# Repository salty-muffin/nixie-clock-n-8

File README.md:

# nixie-clock-n-8
a nixie clock built around 4 IN-8 tubes and an INS-3 dot

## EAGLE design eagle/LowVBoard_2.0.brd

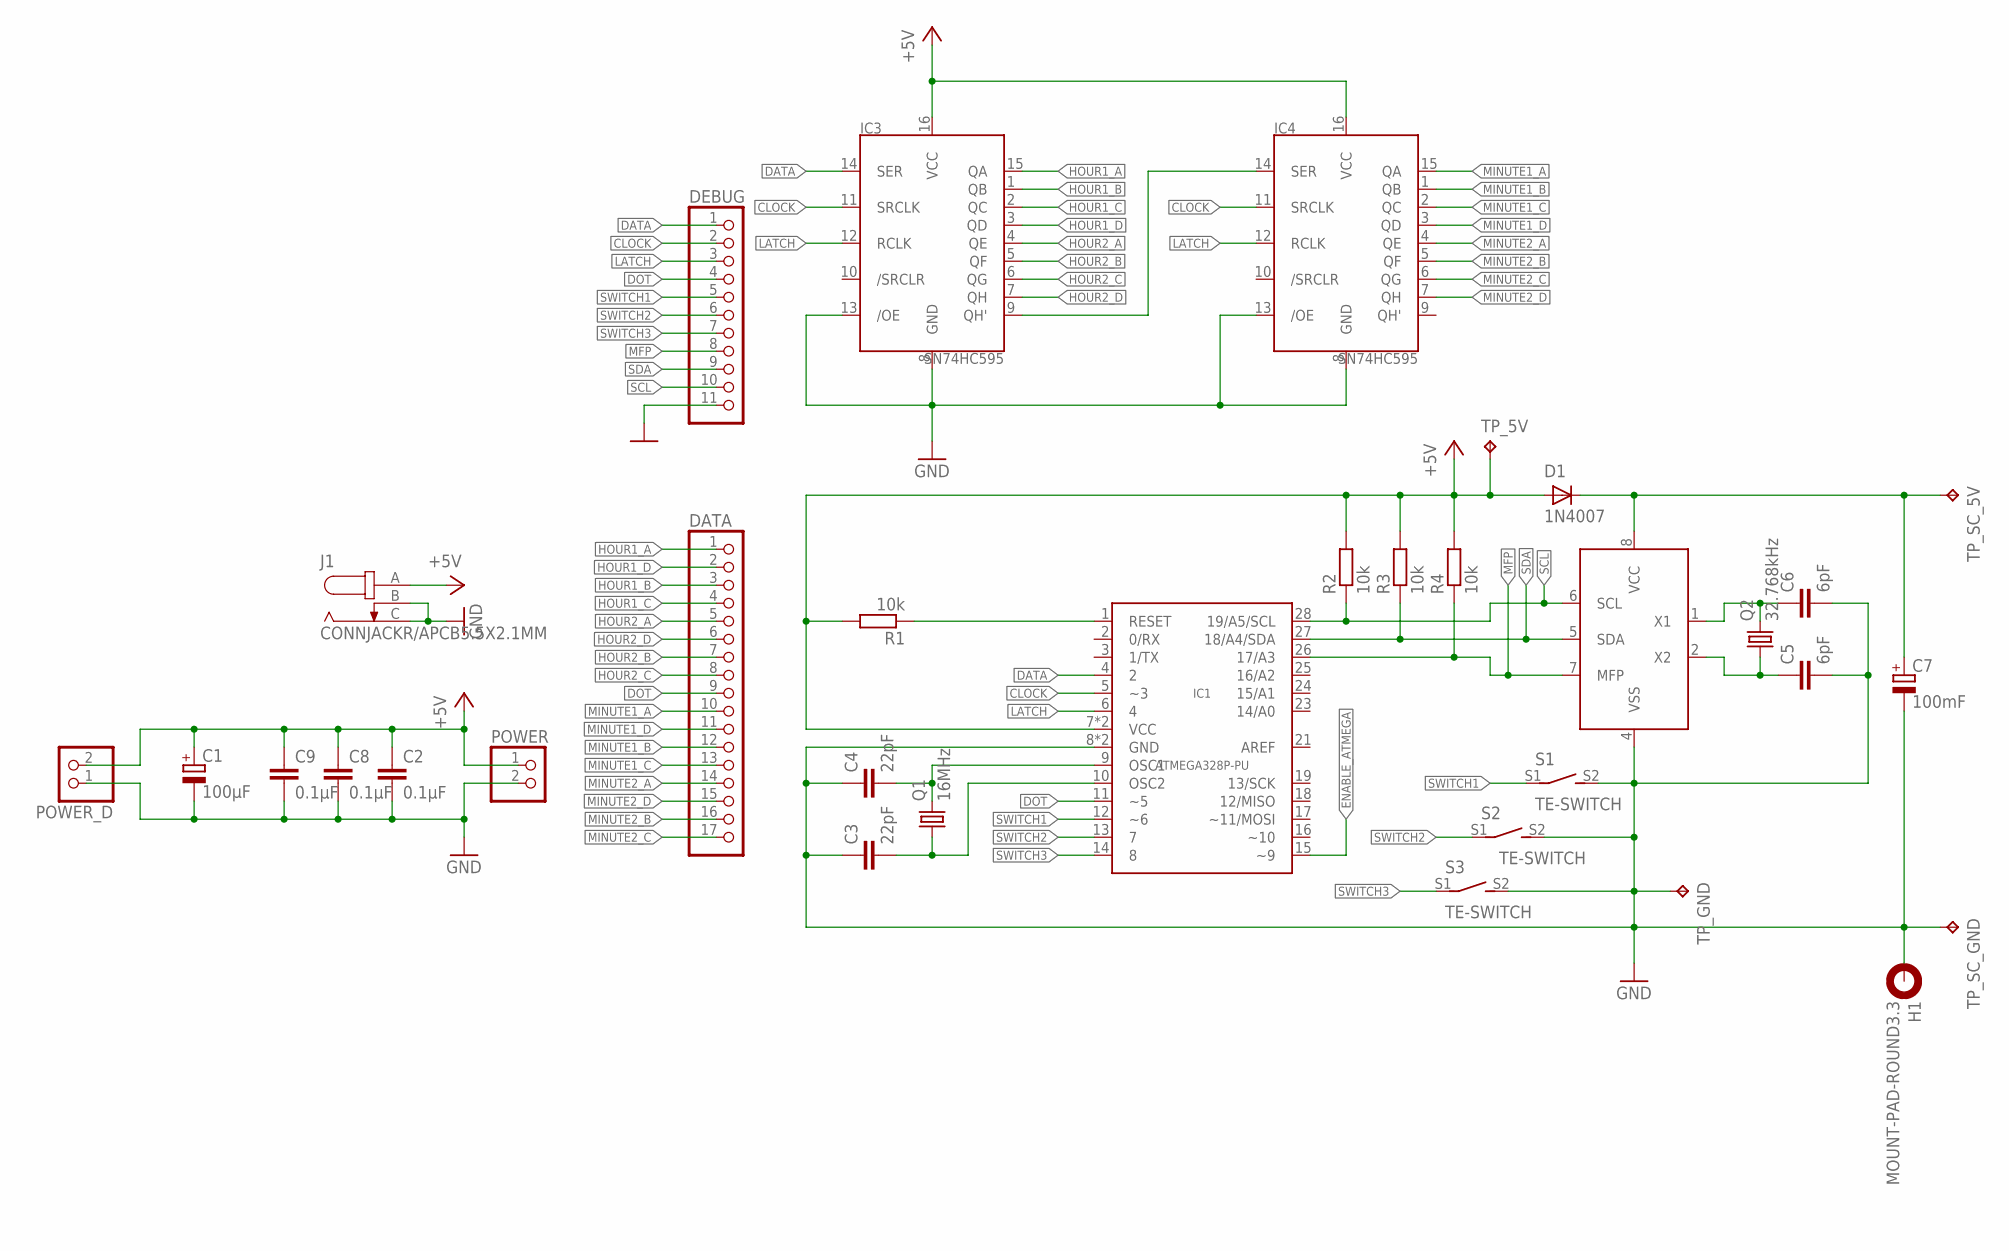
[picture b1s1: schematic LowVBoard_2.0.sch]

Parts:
C1: 100µF; E2-5
C2, C8, C9: 0.1µF; C025-024X044
C3, C4: 22pF; C025-024X044
C5, C6: 6pF; C025-024X044
C7: 100mF; SUPERCAP-11.5
D1: 1N4007; DO41-7.6
DATA: PINHD-1X17; 1X17
DEBUG: PINHD-1X11/90; 1X11/90
H1: MOUNT-PAD-ROUND3.3; 3,3-PAD
IC1: ATMEGA328P-PU; DIP28
IC2: MCP7940M; DIL8
IC3, IC4: SN74HC595; DIL16
J1: CONNJACKR/APCB5.5X2.1MM
POWER: PINHD-1X2; 1X02
POWER_D: PINHD-1X2/90; 1X02/90
Q1: 16MHz; HC49/S
Q2: 32.768kHz; CFS-206
R1, R2, R3, R4: 10k; 0207/7
S1, S2, S3: TE-SWITCH
TP_5V: TPPAD1-13; P1-13
TP_GND: TPPAD1-13; P1-13
TP_SC_5V: TPPAD1-13; P1-13
TP_SC_GND: TPPAD1-13; P1-13

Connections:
+5V: C1.+, C2.1, C8.1, C9.1, D1.A, IC1.7 (VCC), IC1.20 (VCC), IC3.16 (VCC), IC4.16 (VCC), J1.A, POWER.1, POWER_D.2, R1.2, R2.2, R3.2, R4.2, TP_5V.TP
CLOCK: DEBUG.2, IC1.5 (~3), IC3.11 (SRCLK), IC4.11 (SRCLK)
DATA: DEBUG.1, IC1.4 (2), IC3.14 (SER)
DOT: DATA.9, DEBUG.4, IC1.11 (~5)
ENABLE_ATMEGA: IC1.15 (~9)
GND: C1.-, C2.2, C3.1, C4.1, C5.2, C6.2, C7.-, C8.2, C9.2, DEBUG.11, H1.B3,3, IC1.8 (GND), IC1.22 (GND), IC2.4 (VSS), IC3.8 (GND), IC3.13 (/OE), IC4.8 (GND), IC4.13 (/OE), J1.B, J1.C, POWER.2, POWER_D.1, S1.S2 (S), S2.S2 (S), S3.S2 (S), TP_GND.TP, TP_SC_GND.TP
HOUR1_A: DATA.1, IC3.15 (QA)
HOUR1_B: DATA.3, IC3.1 (QB)
HOUR1_C: DATA.4, IC3.2 (QC)
HOUR1_D: DATA.2, IC3.3 (QD)
HOUR2_A: DATA.5, IC3.4 (QE)
HOUR2_B: DATA.7, IC3.5 (QF)
HOUR2_C: DATA.8, IC3.6 (QG)
HOUR2_D: DATA.6, IC3.7 (QH)
LATCH: DEBUG.3, IC1.6 (4), IC3.12 (RCLK), IC4.12 (RCLK)
MFP: DEBUG.8, IC1.26 (17/A3), IC2.7 (MFP), R4.1
MINUTE1_A: DATA.10, IC4.15 (QA)
MINUTE1_B: DATA.12, IC4.1 (QB)
MINUTE1_C: DATA.13, IC4.2 (QC)
MINUTE1_D: DATA.11, IC4.3 (QD)
MINUTE2_A: DATA.14, IC4.4 (QE)
MINUTE2_B: DATA.16, IC4.5 (QF)
MINUTE2_C: DATA.17, IC4.6 (QG)
MINUTE2_D: DATA.15, IC4.7 (QH)
unnamed: C7.+, D1.C, IC2.8 (VCC), TP_SC_5V.TP
unnamed: C4.2, IC1.9 (OSC1), Q1.2
unnamed: C3.2, IC1.10 (OSC2), Q1.1
unnamed: IC1.1 (RESET), R1.1
unnamed: C6.1, IC2.1 (X1), Q2.P$2 (2)
unnamed: C5.1, IC2.2 (X2), Q2.P$1 (1)
unnamed: IC3.9 (QH'), IC4.14 (SER)
SCL: DEBUG.10, IC1.28 (19/A5/SCL), IC2.6 (SCL), R2.1
SDA: DEBUG.9, IC1.27 (18/A4/SDA), IC2.5 (SDA), R3.1
SWITCH1: DEBUG.5, IC1.12 (~6), S1.S1
SWITCH2: DEBUG.6, IC1.13 (7), S2.S1
SWITCH3: DEBUG.7, IC1.14 (8), S3.S1

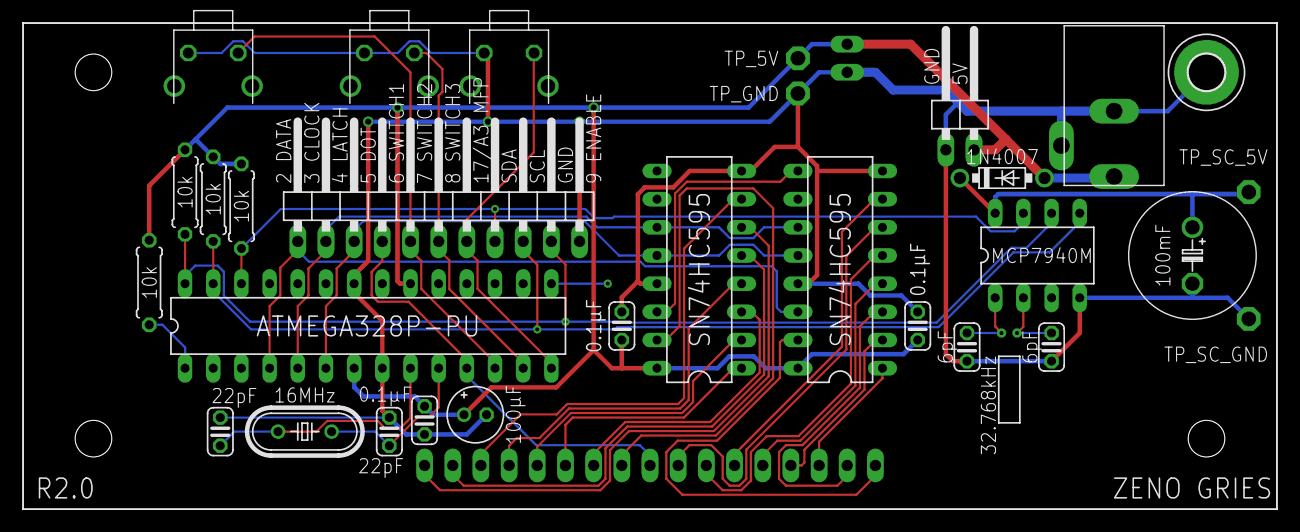
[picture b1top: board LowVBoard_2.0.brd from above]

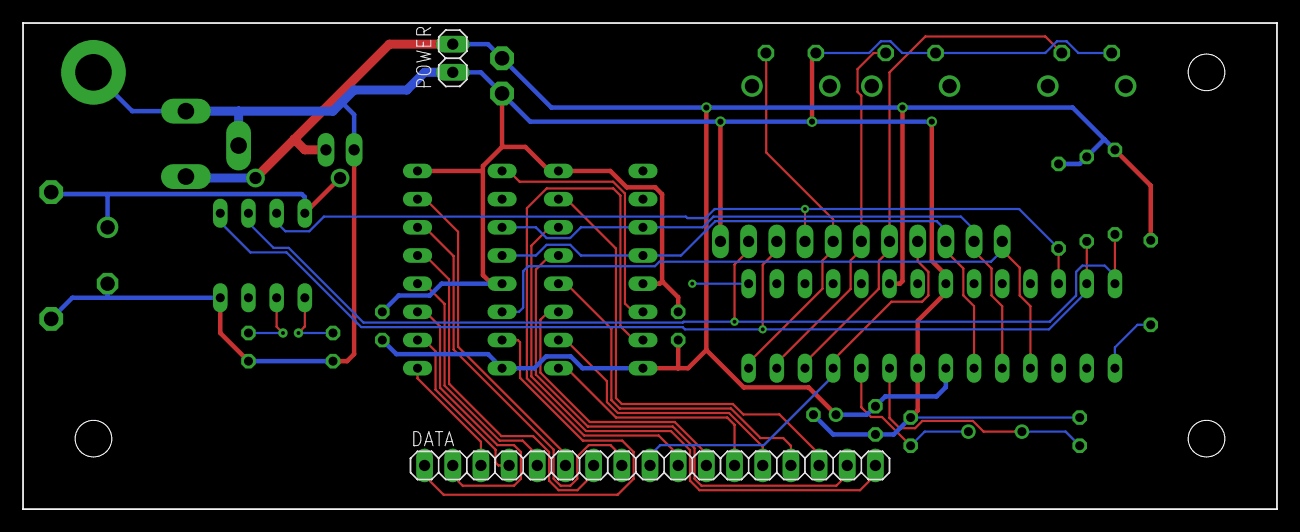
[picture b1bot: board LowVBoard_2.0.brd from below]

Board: 2 copper layers, 113.0 x 43.8 mm, 33 parts (2 on the bottom side), 35 nets.

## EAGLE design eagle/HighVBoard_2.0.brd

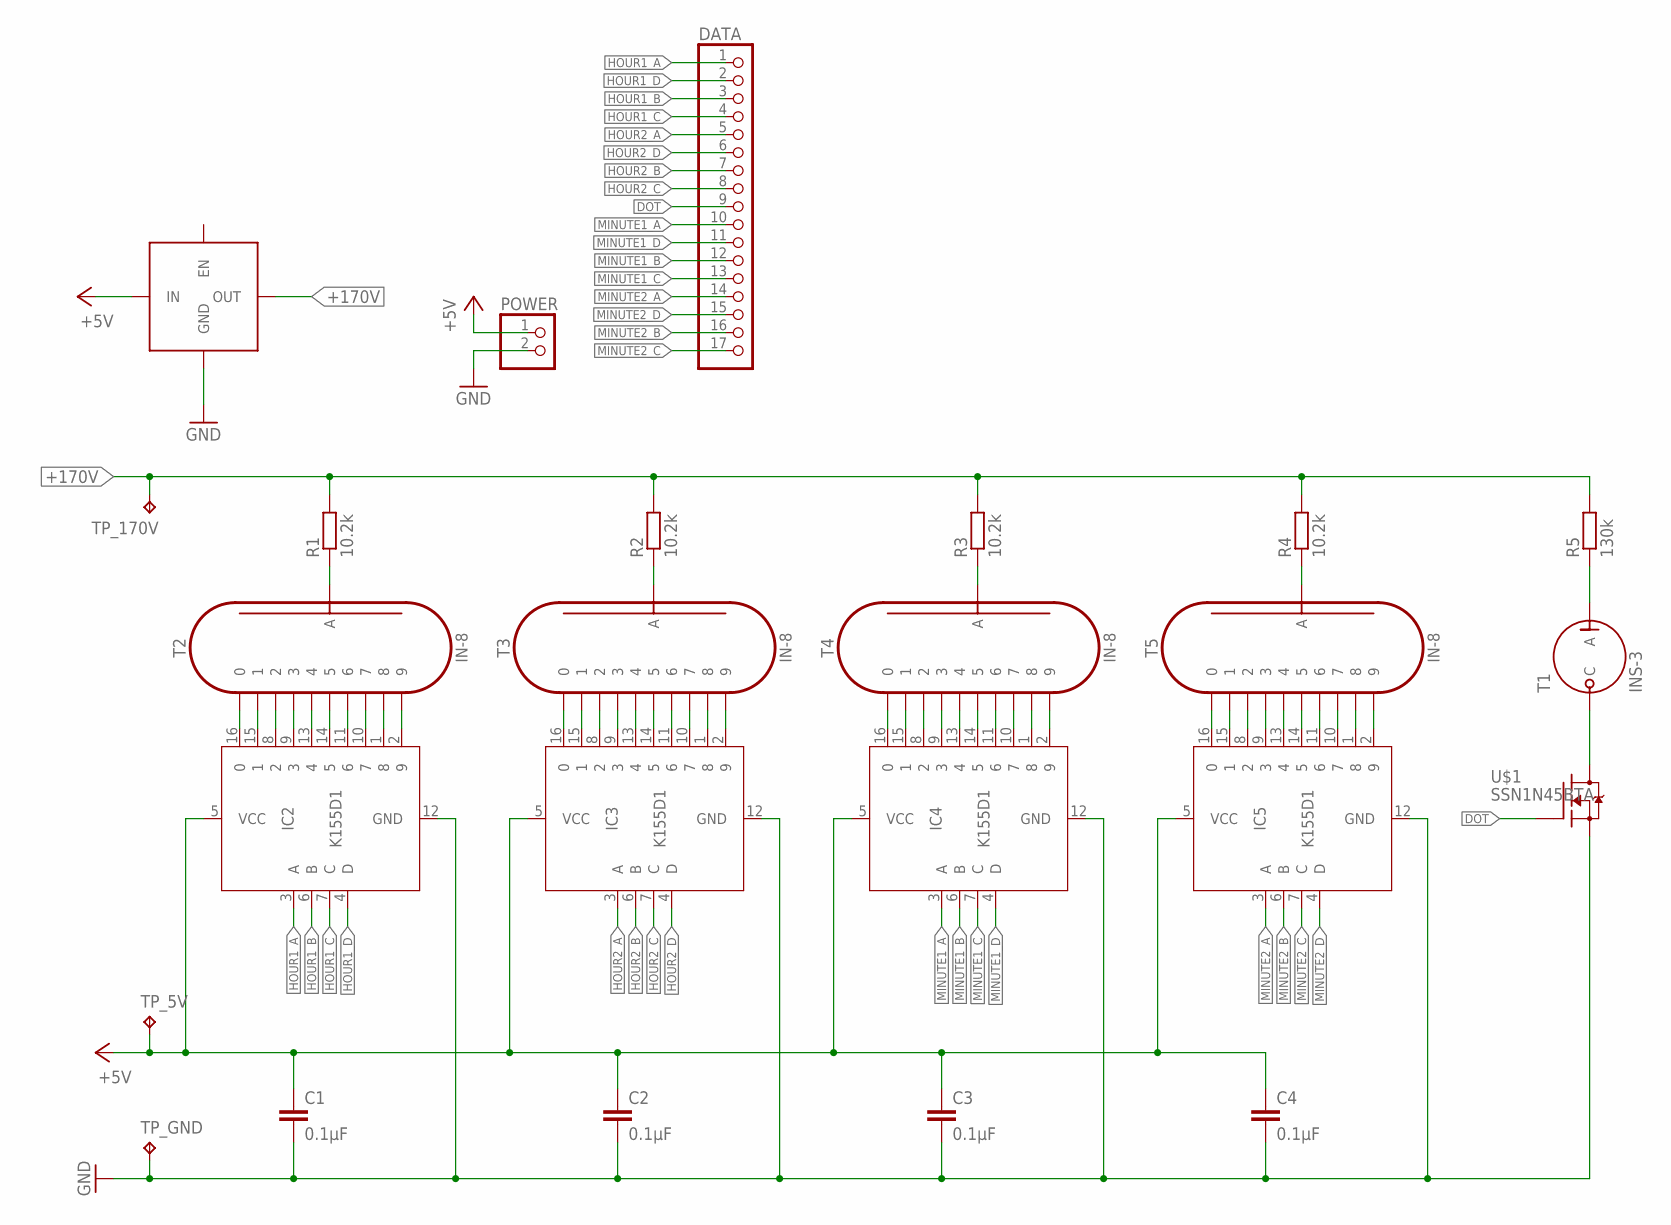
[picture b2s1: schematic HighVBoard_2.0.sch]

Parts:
C1, C2, C3, C4: 0.1µF; C025-024X044
DATA: PINHD-1X17; 1X17
IC2, IC3, IC4, IC5: K155D1; DIL16
POWER: PINHD-1X2; 1X02
R1, R2, R3, R4: 10.2k; 0207/10
R5: 130k; 0207/10
T1: INS-3
T2, T3, T4, T5: IN-8
TP_5V, TP_170V: TPPAD1-13; P1-13
TP_GND: TPPAD1-13; P1-13
U$1: SSN1N45BTA; TO92
U$2: NIXIE-PSU

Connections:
+5V: C1.1, C2.1, C3.1, C4.1, IC2.5 (VCC), IC3.5 (VCC), IC4.5 (VCC), IC5.5 (VCC), POWER.1, TP_5V.TP, U$2.1 (IN)
+170V: R1.2, R2.2, R3.2, R4.2, R5.2, TP_170V.TP, U$2.5 (OUT)
DOT: DATA.9, U$1.1 (G)
GND: C1.2, C2.2, C3.2, C4.2, IC2.12 (GND), IC3.12 (GND), IC4.12 (GND), IC5.12 (GND), POWER.2, TP_GND.TP, U$1.3 (S), U$2.2 (GND), U$2.4 (GND)
HOUR1_A: DATA.1, IC2.3 (A)
HOUR1_B: DATA.3, IC2.6 (B)
HOUR1_C: DATA.4, IC2.7 (C)
HOUR1_D: DATA.2, IC2.4 (D)
HOUR2_A: DATA.5, IC3.3 (A)
HOUR2_B: DATA.7, IC3.6 (B)
HOUR2_C: DATA.8, IC3.7 (C)
HOUR2_D: DATA.6, IC3.4 (D)
MINUTE1_A: DATA.10, IC4.3 (A)
MINUTE1_B: DATA.12, IC4.6 (B)
MINUTE1_C: DATA.13, IC4.7 (C)
MINUTE1_D: DATA.11, IC4.4 (D)
MINUTE2_A: DATA.14, IC5.3 (A)
MINUTE2_B: DATA.16, IC5.6 (B)
MINUTE2_C: DATA.17, IC5.7 (C)
MINUTE2_D: DATA.15, IC5.4 (D)
unnamed: T1.C, U$1.2 (D)
unnamed: IC2.16 (0), T2.10 (0)
unnamed: IC2.15 (1), T2.1
unnamed: IC2.8 (2), T2.2
unnamed: IC2.9 (3), T2.3
unnamed: IC2.13 (4), T2.4
unnamed: IC2.14 (5), T2.5
unnamed: IC2.11 (6), T2.6
unnamed: IC2.10 (7), T2.7
unnamed: IC2.1 (8), T2.8
unnamed: IC2.2 (9), T2.9
unnamed: R1.1, T2.A
unnamed: IC3.16 (0), T3.10 (0)
unnamed: IC3.15 (1), T3.1
unnamed: IC3.8 (2), T3.2
unnamed: IC3.9 (3), T3.3
unnamed: IC3.13 (4), T3.4
unnamed: IC3.14 (5), T3.5
unnamed: IC3.11 (6), T3.6
unnamed: IC3.10 (7), T3.7
unnamed: IC3.1 (8), T3.8
unnamed: IC3.2 (9), T3.9
unnamed: R2.1, T3.A
unnamed: IC4.16 (0), T4.10 (0)
unnamed: IC4.15 (1), T4.1
unnamed: IC4.8 (2), T4.2
unnamed: IC4.9 (3), T4.3
unnamed: IC4.13 (4), T4.4
unnamed: IC4.14 (5), T4.5
unnamed: IC4.11 (6), T4.6
unnamed: IC4.10 (7), T4.7
unnamed: IC4.1 (8), T4.8
unnamed: IC4.2 (9), T4.9
unnamed: R3.1, T4.A
unnamed: IC5.16 (0), T5.10 (0)
unnamed: IC5.15 (1), T5.1
unnamed: IC5.8 (2), T5.2
unnamed: IC5.9 (3), T5.3
unnamed: IC5.13 (4), T5.4
unnamed: IC5.14 (5), T5.5
unnamed: IC5.11 (6), T5.6
unnamed: IC5.10 (7), T5.7
unnamed: IC5.1 (8), T5.8
unnamed: IC5.2 (9), T5.9
unnamed: R4.1, T5.A
unnamed: R5.1, T1.A

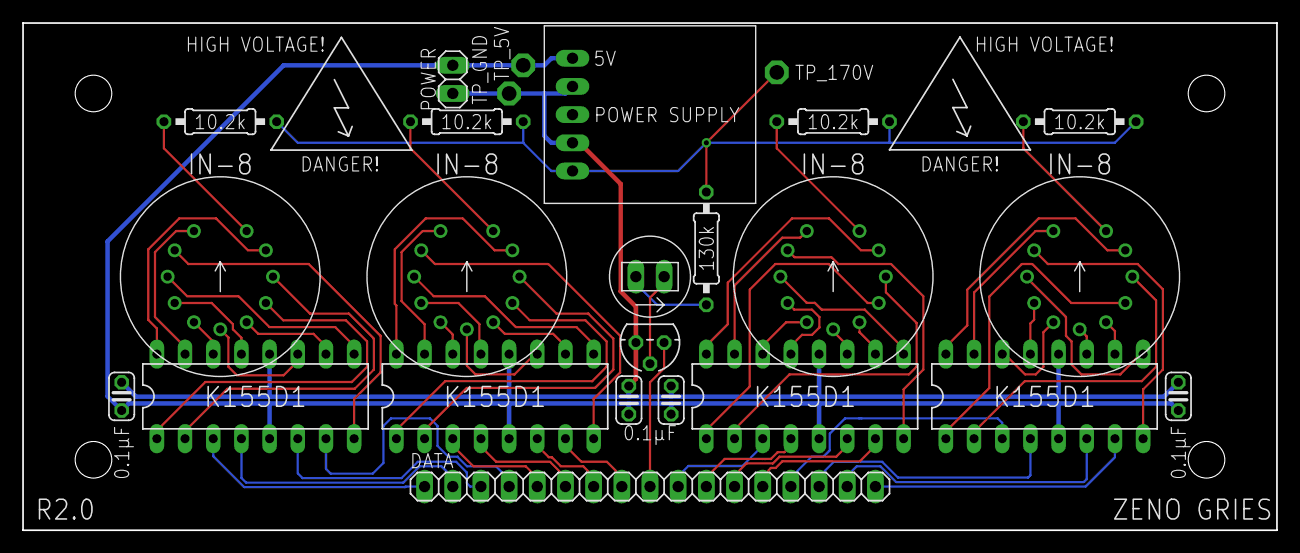
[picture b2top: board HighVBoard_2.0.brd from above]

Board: 2 copper layers, 113.0 x 45.7 mm, 25 parts (0 on the bottom side), 66 nets.

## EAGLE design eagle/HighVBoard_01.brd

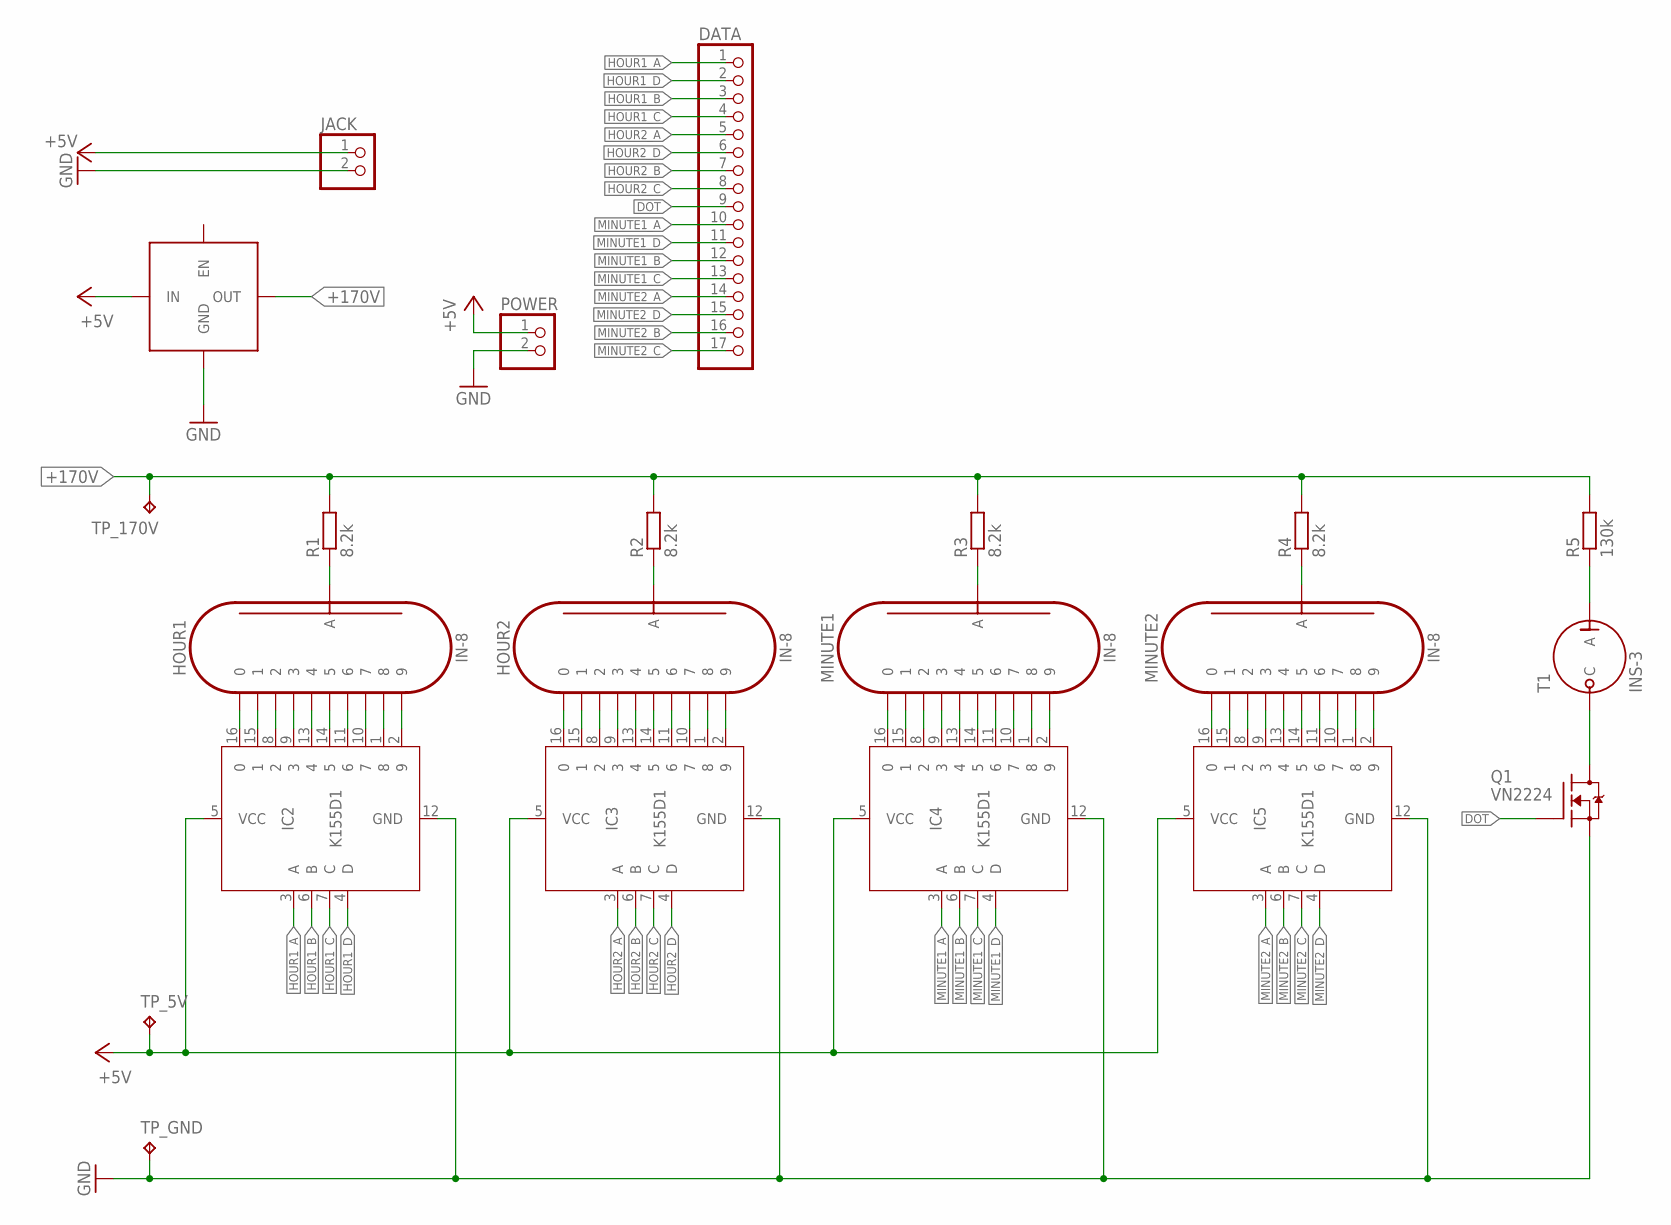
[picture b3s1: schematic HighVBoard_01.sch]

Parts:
DATA: PINHD-1X17; 1X17
HOUR1, HOUR2: IN-8
IC2, IC3, IC4, IC5: K155D1; DIL16
JACK: PINHD-1X2/90; 1X02/90
MINUTE1, MINUTE2: IN-8
POWER: PINHD-1X2; 1X02
Q1: VN2224; TO92
R1, R2, R3, R4: 8.2k; 0207/10
R5: 130k; 0207/10
T1: INS-3
TP_5V, TP_170V: TPPAD1-13; P1-13
TP_GND: TPPAD1-13; P1-13
U$1: NIXIE-PSU

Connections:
+5V: IC2.5 (VCC), IC3.5 (VCC), IC4.5 (VCC), IC5.5 (VCC), JACK.1, POWER.1, TP_5V.TP, U$1.1 (IN)
+170V: R1.2, R2.2, R3.2, R4.2, R5.2, TP_170V.TP, U$1.5 (OUT)
DOT: DATA.9, Q1.2 (G)
GND: IC2.12 (GND), IC3.12 (GND), IC4.12 (GND), IC5.12 (GND), JACK.2, POWER.2, Q1.1 (S), TP_GND.TP, U$1.2 (GND), U$1.4 (GND)
HOUR1_A: DATA.1, IC2.3 (A)
HOUR1_B: DATA.3, IC2.6 (B)
HOUR1_C: DATA.4, IC2.7 (C)
HOUR1_D: DATA.2, IC2.4 (D)
HOUR2_A: DATA.5, IC3.3 (A)
HOUR2_B: DATA.7, IC3.6 (B)
HOUR2_C: DATA.8, IC3.7 (C)
HOUR2_D: DATA.6, IC3.4 (D)
MINUTE1_A: DATA.10, IC4.3 (A)
MINUTE1_B: DATA.12, IC4.6 (B)
MINUTE1_C: DATA.13, IC4.7 (C)
MINUTE1_D: DATA.11, IC4.4 (D)
MINUTE2_A: DATA.14, IC5.3 (A)
MINUTE2_B: DATA.16, IC5.6 (B)
MINUTE2_C: DATA.17, IC5.7 (C)
MINUTE2_D: DATA.15, IC5.4 (D)
unnamed: Q1.3 (D), T1.C
unnamed: HOUR1.10 (0), IC2.16 (0)
unnamed: HOUR1.1, IC2.15 (1)
unnamed: HOUR1.2, IC2.8 (2)
unnamed: HOUR1.3, IC2.9 (3)
unnamed: HOUR1.4, IC2.13 (4)
unnamed: HOUR1.5, IC2.14 (5)
unnamed: HOUR1.6, IC2.11 (6)
unnamed: HOUR1.7, IC2.10 (7)
unnamed: HOUR1.8, IC2.1 (8)
unnamed: HOUR1.9, IC2.2 (9)
unnamed: HOUR1.A, R1.1
unnamed: HOUR2.10 (0), IC3.16 (0)
unnamed: HOUR2.1, IC3.15 (1)
unnamed: HOUR2.2, IC3.8 (2)
unnamed: HOUR2.3, IC3.9 (3)
unnamed: HOUR2.4, IC3.13 (4)
unnamed: HOUR2.5, IC3.14 (5)
unnamed: HOUR2.6, IC3.11 (6)
unnamed: HOUR2.7, IC3.10 (7)
unnamed: HOUR2.8, IC3.1 (8)
unnamed: HOUR2.9, IC3.2 (9)
unnamed: HOUR2.A, R2.1
unnamed: IC4.16 (0), MINUTE1.10 (0)
unnamed: IC4.15 (1), MINUTE1.1
unnamed: IC4.8 (2), MINUTE1.2
unnamed: IC4.9 (3), MINUTE1.3
unnamed: IC4.13 (4), MINUTE1.4
unnamed: IC4.14 (5), MINUTE1.5
unnamed: IC4.11 (6), MINUTE1.6
unnamed: IC4.10 (7), MINUTE1.7
unnamed: IC4.1 (8), MINUTE1.8
unnamed: IC4.2 (9), MINUTE1.9
unnamed: MINUTE1.A, R3.1
unnamed: IC5.16 (0), MINUTE2.10 (0)
unnamed: IC5.15 (1), MINUTE2.1
unnamed: IC5.8 (2), MINUTE2.2
unnamed: IC5.9 (3), MINUTE2.3
unnamed: IC5.13 (4), MINUTE2.4
unnamed: IC5.14 (5), MINUTE2.5
unnamed: IC5.11 (6), MINUTE2.6
unnamed: IC5.10 (7), MINUTE2.7
unnamed: IC5.1 (8), MINUTE2.8
unnamed: IC5.2 (9), MINUTE2.9
unnamed: MINUTE2.A, R4.1
unnamed: R5.1, T1.A

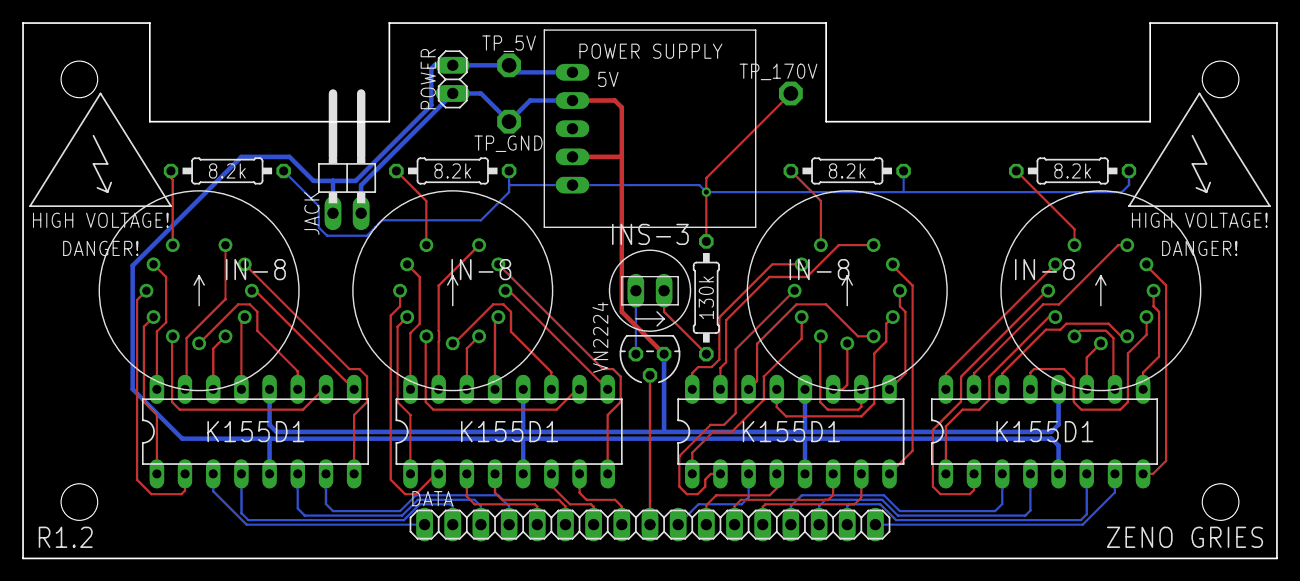
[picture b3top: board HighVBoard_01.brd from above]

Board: 2 copper layers, 113.0 x 48.3 mm, 22 parts (0 on the bottom side), 66 nets.

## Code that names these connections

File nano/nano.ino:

#include <MCP7940.h>

#define LED     13
#define DOT     17
#define DATA    2
#define CLOCK   3
#define LATCH   4
#define SWITCH1 6
#define SWITCH2 7
#define SWITCH3 8

MCP7940_Class MCP7940;

void writeTime(uint8_t hour, uint8_t minute) {
  uint8_t hour1 = hour / 10;
  uint8_t hour2 = hour % 10;
  uint8_t minute1 = minute / 10;
  uint8_t minute2 = minute % 10;

  uint8_t hourBinary = hour1 << 4 | hour2;
  uint8_t minuteBinary = minute1 << 4 | minute2;

  // shift out
  digitalWrite(LATCH, LOW);

  shiftOut(DATA, CLOCK, LSBFIRST, minuteBinary);
  shiftOut(DATA, CLOCK, LSBFIRST, hourBinary);

  digitalWrite(LATCH, HIGH);
}

void setup() {
  Serial.begin(9600);

  // set pins
  pinMode(LED, OUTPUT);
  pinMode(DOT, OUTPUT);
  pinMode(DATA, OUTPUT);
  pinMode(CLOCK, OUTPUT);
  pinMode(LATCH, OUTPUT);

  // connect to rtc
  Serial.println("Connecting to rtc...");
  while (!MCP7940.begin()) {
    Serial.println("Unable to find rtc. Checking again in 1 second.");
    delay(1000);
  }

  // if connected, turn dot on and start rtc
  Serial.println("Starting oscillator...");
  if(!MCP7940.deviceStart()) Serial.println("Unable to start oscillator");
}

void loop() {
  // get time from rtc
  DateTime now = MCP7940.now();

  // debug
  // Serial.println("H: " + String(now.hour()) +
  //                "\tM: " + String(now.minute()) +
  //                "\tS: " + String(now.second()));

  writeTime(now.minute(), now.second());

  digitalWrite(DOT, HIGH);
  delay(500);
  digitalWrite(DOT, LOW);
  delay(500);
}

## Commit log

2019-10-23 pcbs
2019-10-23 script
2019-10-23 empty partslist added
2019-11-15 pcb updates
2019-11-16 partslists
2019-12-02 corrected pcb
2020-01-08 comoved two way buttons
2020-01-13 updated pcb and partslist
2020-01-15 updated pcb
2020-01-15 added test
2020-09-10 beauty changes
2020-11-29 new boards
2020-12-19 finished
2020-12-21 added new formfactor boards
2020-12-21 added clearance for wodden board in front of switches and jack
2023-08-29 added kicad files
2023-08-30 new design
2023-08-30 removed backups
2023-09-05 added partslist
2023-09-05 setup board
2023-09-09 finished routing
2023-09-09 added TPIC6B595
2023-09-18 started on new script
2023-09-19 finished pcb
2024-01-03 added acrylic cuts
2024-01-04 added new cuts
